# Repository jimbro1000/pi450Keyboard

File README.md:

# PI450 Mechanical Keyboard #

## Status ##
This is an exploratory, experimental design,
mostly to prove how quick and easy it is to design
keyboard hardware

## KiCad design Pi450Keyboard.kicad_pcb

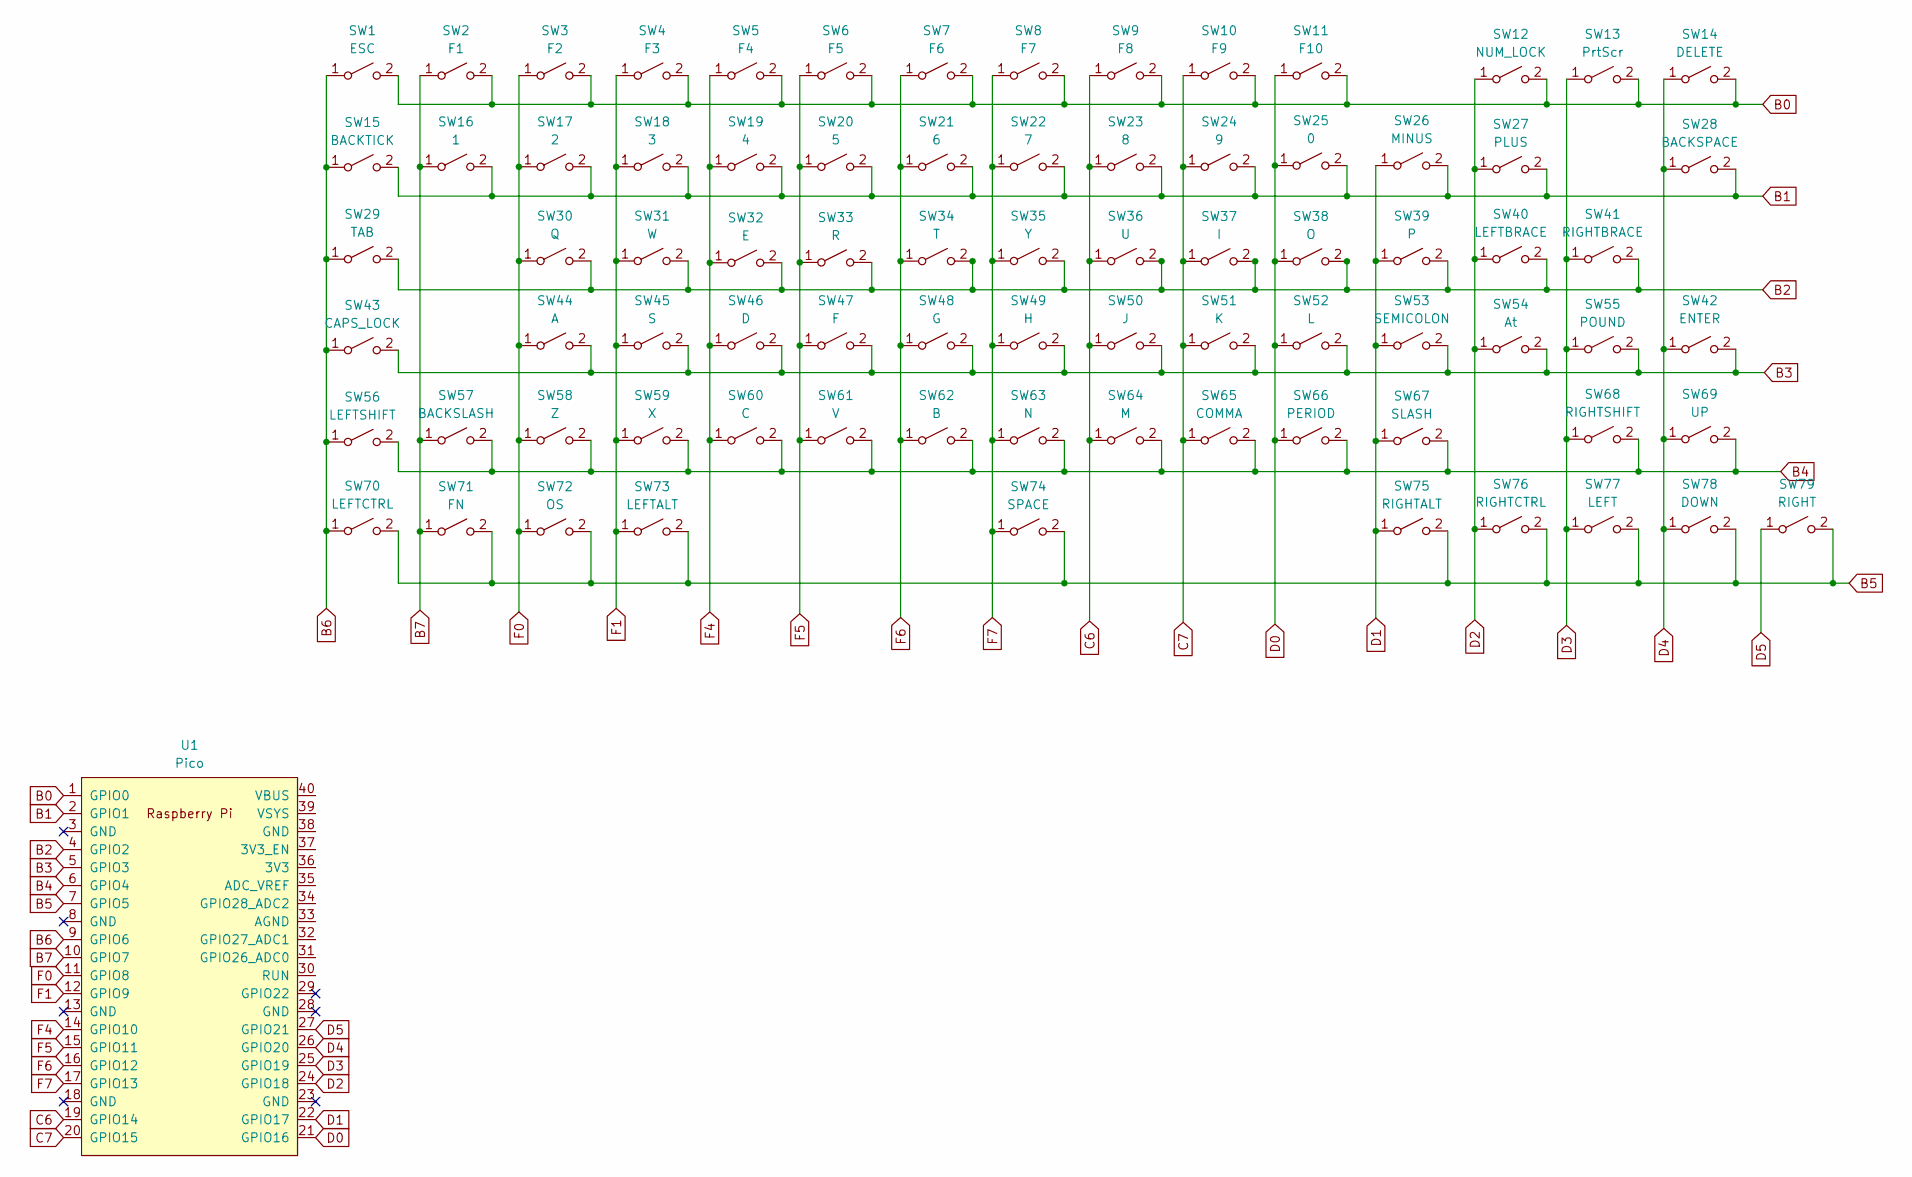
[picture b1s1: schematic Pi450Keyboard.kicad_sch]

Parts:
SW1: ESC; SW_Cherry_MX_1.00u_PCB
SW2: F1; SW_Cherry_MX_1.00u_PCB
SW3: F2; SW_Cherry_MX_1.00u_PCB
SW4: F3; SW_Cherry_MX_1.00u_PCB
SW5: F4; SW_Cherry_MX_1.00u_PCB
SW6: F5; SW_Cherry_MX_1.00u_PCB
SW7: F6; SW_Cherry_MX_1.00u_PCB
SW8: F7; SW_Cherry_MX_1.00u_PCB
SW9: F8; SW_Cherry_MX_1.00u_PCB
SW10: F9; SW_Cherry_MX_1.00u_PCB
SW11: F10; SW_Cherry_MX_1.00u_PCB
SW12: NUM_LOCK; SW_Cherry_MX_1.00u_PCB
SW13: PrtScr; SW_Cherry_MX_1.00u_PCB
SW14: DELETE; SW_Cherry_MX_1.00u_PCB
SW15: BACKTICK; SW_Cherry_MX_1.00u_PCB
SW16: 1; SW_Cherry_MX_1.00u_PCB
SW17: 2; SW_Cherry_MX_1.00u_PCB
SW18: 3; SW_Cherry_MX_1.00u_PCB
SW19: 4; SW_Cherry_MX_1.00u_PCB
SW20: 5; SW_Cherry_MX_1.00u_PCB
SW21: 6; SW_Cherry_MX_1.00u_PCB
SW22: 7; SW_Cherry_MX_1.00u_PCB
SW23: 8; SW_Cherry_MX_1.00u_PCB
SW24: 9; SW_Cherry_MX_1.00u_PCB
SW25: 0; SW_Cherry_MX_1.00u_PCB
SW26: MINUS; SW_Cherry_MX_1.00u_PCB
SW27: PLUS; SW_Cherry_MX_1.00u_PCB
SW28: BACKSPACE; SW_Cherry_MX_2.00u_PCB
SW29: TAB; SW_Cherry_MX_1.50u_PCB
SW30: Q; SW_Cherry_MX_1.00u_PCB
SW31: W; SW_Cherry_MX_1.00u_PCB
SW32: E; SW_Cherry_MX_1.00u_PCB
SW33: R; SW_Cherry_MX_1.00u_PCB
SW34: T; SW_Cherry_MX_1.00u_PCB
SW35: Y; SW_Cherry_MX_1.00u_PCB
SW36: U; SW_Cherry_MX_1.00u_PCB
SW37: I; SW_Cherry_MX_1.00u_PCB
SW38: O; SW_Cherry_MX_1.00u_PCB
SW39: P; SW_Cherry_MX_1.00u_PCB
SW40: LEFTBRACE; SW_Cherry_MX_1.00u_PCB
SW41: RIGHTBRACE; SW_Cherry_MX_1.00u_PCB
SW42: ENTER; SW_Cherry_MX_2.00u_Vertical_PCB
SW43: CAPS_LOCK; SW_Cherry_MX_1.75u_PCB
SW44: A; SW_Cherry_MX_1.00u_PCB
SW45: S; SW_Cherry_MX_1.00u_PCB
SW46: D; SW_Cherry_MX_1.00u_PCB
SW47: F; SW_Cherry_MX_1.00u_PCB
SW48: G; SW_Cherry_MX_1.00u_PCB
SW49: H; SW_Cherry_MX_1.00u_PCB
SW50: J; SW_Cherry_MX_1.00u_PCB
SW51: K; SW_Cherry_MX_1.00u_PCB
SW52: L; SW_Cherry_MX_1.00u_PCB
SW53: SEMICOLON; SW_Cherry_MX_1.00u_PCB
SW54: At; SW_Cherry_MX_1.00u_PCB
SW55: POUND; SW_Cherry_MX_1.00u_PCB
SW56: LEFTSHIFT; SW_Cherry_MX_1.25u_PCB
SW57: BACKSLASH; SW_Cherry_MX_1.00u_PCB
SW58: Z; SW_Cherry_MX_1.00u_PCB
SW59: X; SW_Cherry_MX_1.00u_PCB
SW60: C; SW_Cherry_MX_1.00u_PCB
SW61: V; SW_Cherry_MX_1.00u_PCB
SW62: B; SW_Cherry_MX_1.00u_PCB
SW63: N; SW_Cherry_MX_1.00u_PCB
SW64: M; SW_Cherry_MX_1.00u_PCB
SW65: COMMA; SW_Cherry_MX_1.00u_PCB
SW66: PERIOD; SW_Cherry_MX_1.00u_PCB
SW67: SLASH; SW_Cherry_MX_1.00u_PCB
SW68: RIGHTSHIFT; SW_Cherry_MX_1.50u_PCB
SW69: UP; SW_Cherry_MX_1.00u_PCB
SW70: LEFTCTRL; SW_Cherry_MX_1.00u_PCB
SW71: FN; SW_Cherry_MX_1.00u_PCB
SW72: OS; SW_Cherry_MX_1.00u_PCB
SW73: LEFTALT; SW_Cherry_MX_1.25u_PCB
SW74: SPACE; SW_Cherry_MX_6.25u_PCB
SW75: RIGHTALT; SW_Cherry_MX_1.25u_PCB
SW76: RIGHTCTRL; SW_Cherry_MX_1.00u_PCB
SW77: LEFT; SW_Cherry_MX_1.00u_PCB
SW78: DOWN; SW_Cherry_MX_1.00u_PCB
SW79: RIGHT; SW_Cherry_MX_1.00u_PCB
U1: Pico; RPi_Pico_SMD_TH

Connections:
B0: SW1.2 (B), SW2.2 (B), SW3.2 (B), SW4.2 (B), SW5.2 (B), SW6.2 (B), SW7.2 (B), SW8.2 (B), SW9.2 (B), SW10.2 (B), SW11.2 (B), SW12.2 (B), SW13.2 (B), SW14.2 (B), U1.1 (GPIO0)
B1: SW15.2 (B), SW16.2 (B), SW17.2 (B), SW18.2 (B), SW19.2 (B), SW20.2 (B), SW21.2 (B), SW22.2 (B), SW23.2 (B), SW24.2 (B), SW25.2 (B), SW26.2 (B), SW27.2 (B), SW28.2 (B), U1.2 (GPIO1)
B2: SW29.2 (B), SW30.2 (B), SW31.2 (B), SW32.2 (B), SW33.2 (B), SW34.2 (B), SW35.2 (B), SW36.2 (B), SW37.2 (B), SW38.2 (B), SW39.2 (B), SW40.2 (B), SW41.2 (B), U1.4 (GPIO2)
B3: SW42.2 (B), SW43.2 (B), SW44.2 (B), SW45.2 (B), SW46.2 (B), SW47.2 (B), SW48.2 (B), SW49.2 (B), SW50.2 (B), SW51.2 (B), SW52.2 (B), SW53.2 (B), SW54.2 (B), SW55.2 (B), U1.5 (GPIO3)
B4: SW56.2 (B), SW57.2 (B), SW58.2 (B), SW59.2 (B), SW60.2 (B), SW61.2 (B), SW62.2 (B), SW63.2 (B), SW64.2 (B), SW65.2 (B), SW66.2 (B), SW67.2 (B), SW68.2 (B), SW69.2 (B), U1.6 (GPIO4)
B5: SW70.2 (B), SW71.2 (B), SW72.2 (B), SW73.2 (B), SW74.2 (B), SW75.2 (B), SW76.2 (B), SW77.2 (B), SW78.2 (B), SW79.2 (B), U1.7 (GPIO5)
B6: SW1.1 (A), SW15.1 (A), SW29.1 (A), SW43.1 (A), SW56.1 (A), SW70.1 (A), U1.9 (GPIO6)
B7: SW2.1 (A), SW16.1 (A), SW57.1 (A), SW71.1 (A), U1.10 (GPIO7)
C6: SW9.1 (A), SW23.1 (A), SW36.1 (A), SW50.1 (A), SW64.1 (A), U1.19 (GPIO14)
C7: SW10.1 (A), SW24.1 (A), SW37.1 (A), SW51.1 (A), SW65.1 (A), U1.20 (GPIO15)
D0: SW11.1 (A), SW25.1 (A), SW38.1 (A), SW52.1 (A), SW66.1 (A), U1.21 (GPIO16)
D1: SW26.1 (A), SW39.1 (A), SW53.1 (A), SW67.1 (A), SW75.1 (A), U1.22 (GPIO17)
D2: SW12.1 (A), SW27.1 (A), SW40.1 (A), SW54.1 (A), SW76.1 (A), U1.24 (GPIO18)
D3: SW13.1 (A), SW41.1 (A), SW55.1 (A), SW68.1 (A), SW77.1 (A), U1.25 (GPIO19)
D4: SW14.1 (A), SW28.1 (A), SW42.1 (A), SW69.1 (A), SW78.1 (A), U1.26 (GPIO20)
D5: SW79.1 (A), U1.27 (GPIO21)
F0: SW3.1 (A), SW17.1 (A), SW30.1 (A), SW44.1 (A), SW58.1 (A), SW72.1 (A), U1.11 (GPIO8)
F1: SW4.1 (A), SW18.1 (A), SW31.1 (A), SW45.1 (A), SW59.1 (A), SW73.1 (A), U1.12 (GPIO9)
F4: SW5.1 (A), SW19.1 (A), SW32.1 (A), SW46.1 (A), SW60.1 (A), U1.14 (GPIO10)
F5: SW6.1 (A), SW20.1 (A), SW33.1 (A), SW47.1 (A), SW61.1 (A), U1.15 (GPIO11)
F6: SW7.1 (A), SW21.1 (A), SW34.1 (A), SW48.1 (A), SW62.1 (A), U1.16 (GPIO12)
F7: SW8.1 (A), SW22.1 (A), SW35.1 (A), SW49.1 (A), SW63.1 (A), SW74.1 (A), U1.17 (GPIO13)

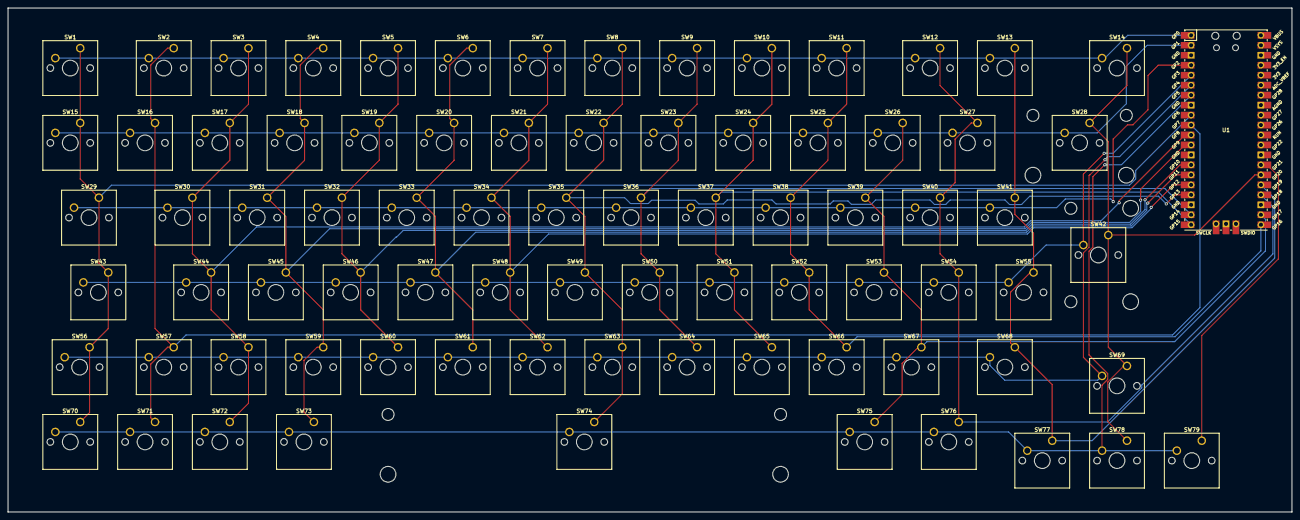
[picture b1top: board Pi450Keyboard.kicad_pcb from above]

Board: 2 copper layers, 327.1 x 128.4 mm, 80 parts (0 on the bottom side), 22 nets.
